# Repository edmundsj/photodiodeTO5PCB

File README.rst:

TO-5 Photodiode Breakout Board
=================================

This PCB is used for a 3-pin TO-5 photodiode breakout board with SMA output. The cathode is connected to the diode case and grounded for better shielding, the traces are kept as short as possible, and the board is kept as compact as possible. 

Features:
-------------
- Extremely compact design (19mm x 18mm)
- ESD protection with optional low-noise SMD diodes and series resistor
- Grounded M3 holes for mounting / housing connection
- SMA output

Bill of Materials
-------------------
.. csv-table:: Bill of Materials
    :widths: 25 25 25 25 25
    :header-rows: 1
    :file: bom.csv

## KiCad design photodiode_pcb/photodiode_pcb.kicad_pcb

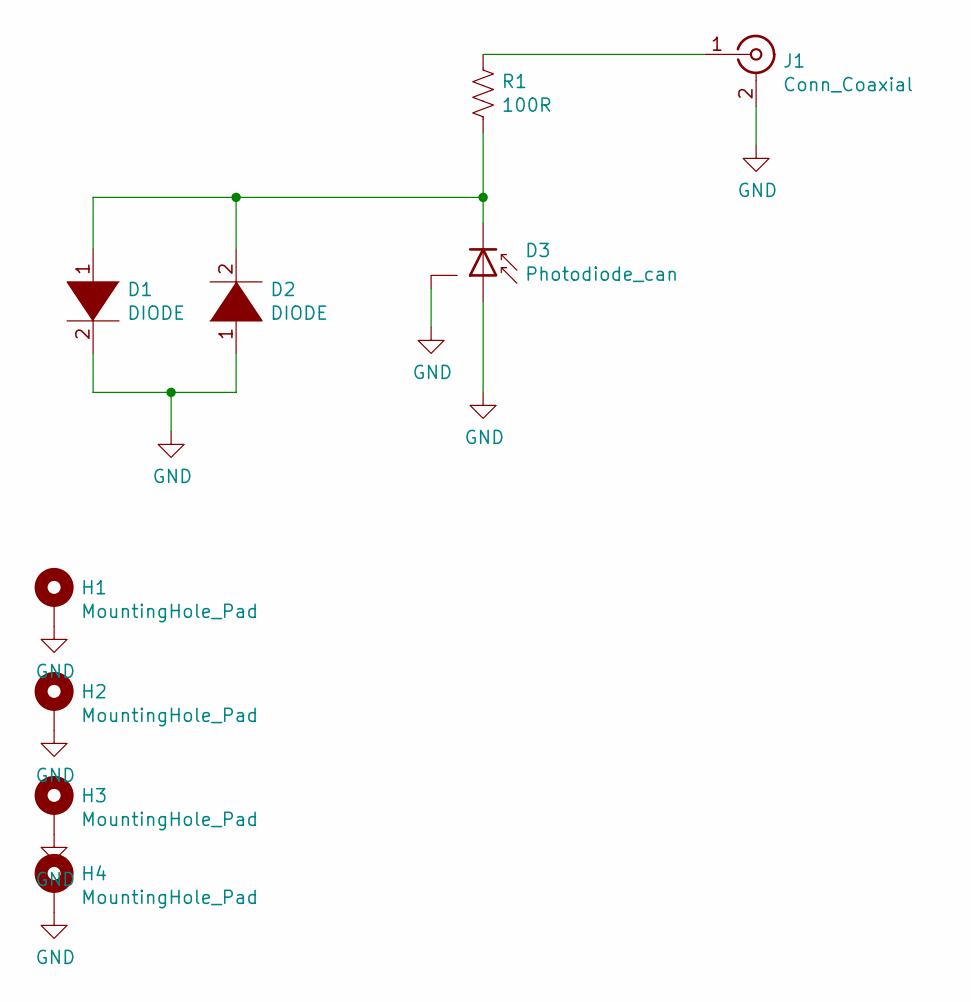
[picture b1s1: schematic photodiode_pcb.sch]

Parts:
D1, D2: DIODE; D_SOD-123
D3: Photodiode_can; TO-46-3_Window
H1, H2, H3, H4: MountingHole_Pad; m3_mounting_hole
J1: Conn_Coaxial; CON-SMA-EDGE-S
R1: 100R; R_0805_2012Metric_Pad1.15x1.40mm_HandSolder

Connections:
GND: D1.2 (A), D2.1 (K), D3.1 (A), D3.3 (CAN), H1.1, H2.1, H3.1, H4.1, J1.2 (Ext)
unnamed: D1.1 (K), D2.2 (A), D3.2 (K), R1.2
unnamed: J1.1 (In), R1.1

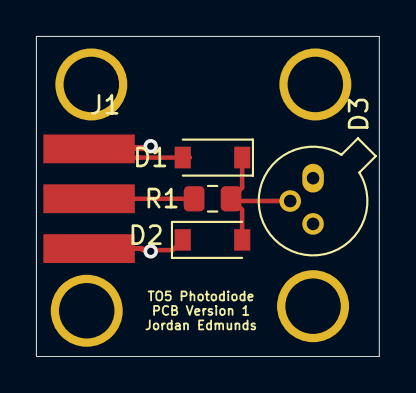
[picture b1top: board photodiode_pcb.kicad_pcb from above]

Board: 2 copper layers, 19.1 x 17.8 mm, 9 parts (0 on the bottom side), 3 nets.

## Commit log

2020-10-21 first commit with README and bill of materials
2020-10-22 added all files for first version of photodiode PCB.
2021-01-19 old update. Not sure what it contains
